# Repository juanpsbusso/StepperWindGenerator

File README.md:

# Stepper Wind Generator o Generador Eólico DIY con Motor Paso a Paso

Este proyecto detalla la construcción de un generador eólico compacto y de bajo coste, diseñado para montarse en cualquier lugar y alimentar luces LED decorativas o un circuito de carga de baterías. Utiliza un motor paso a paso trifásico como generador, aprovechando su capacidad para generar tensión a bajas RPM.

## Motivación y Contexto

Vivo en una zona con vientos constantes. La idea de este proyecto surgió al ver el viento y pensar que podría tener una aplicación práctica y visual. Este pequeño generador, montado en el auto, no solo enciende unas luces LED para darle un aspecto genial, sino que la intensidad de las luces o la cantidad de LEDs que se encienden nos permite inferir la velocidad relativa del viento, convirtiéndolo en un 'anemómetro lumínico' visual.

## ¿Cómo Funciona?

## Principio de Generación

El corazón del sistema es un motor paso a paso. Cuando el eje del motor es girado por la fuerza del viento (mediante las aspas), el motor actúa como un generador de corriente alterna (AC). Dependiendo del modelo de motor, este entregará una tensión alterna multifásica. En mi caso, el motor específico que estoy utilizando es de tres fases, por lo que genera corriente alterna trifásica.

## El Corazón Eléctrico (El Rectificador Trifásico)

Para poder alimentar dispositivos de corriente continua (DC), como luces LED o cargar una batería, necesitamos convertir la AC trifásica que entrega el motor en una tensión DC estable. Para ello, he diseñado e implementado un rectificador trifásico de onda completa.

Utilicé una simulación (ver la Figura 1) para validar el diseño antes de construirlo. El circuito incluye:

* Un puente de diodos Schottky de baja caída (D1-D6) para rectificar la señal.

* Un regulador de tensión ajustable (U1, LM317H) para controlar la tensión de salida.

* Un circuito de control de carga basado en un transistor (Q1) y resistencias ajustables, diseñado originalmente para cargar una batería de 3.7V. Este circuito se puede adaptar fácilmente para controlar la intensidad de las luces LED.

<p align="center">
  <em>Figura 1: Esquema de simulación del rectificador trifásico de onda completa.</em>
</p>

## De la Simulación a la Realidad: PCB y Perfboard

Para pasar del diseño al prototipo, realicé el diseño de una placa de circuito impreso (PCB) utilizando KiCad. El diseño de la PCB está disponible en la carpeta hw/ del repositorio para aquellos que deseen fabricarlo.

<p align="center">
  <em>Figura 2: PCB diseñado en KiCad.</em>
</p>

Sin embargo, para la construcción inicial y pruebas rápidas, decidí armar el circuito en una perfboard (ver Figura 3). Esto demuestra la viabilidad del diseño incluso sin una fabricación de PCB profesional, utilizando componentes estándar y soldadura punto a punto.

<p align="center">
  <em>Figura 3: Vista detallada del prototipo físico montado en perfboard y su conexión a los módulos LED.</em>
</p>

| Componente | Descripción | Cantidad |
| :--- | :--- | :--- |
| **D1-D6** | 1N5819G (Diodos Schottky) | 6 |
| **C1** | 10µF (Capacitor de desacoplo) | 1 |
| **-** | Placas LED (extraídas de óptica de vehículo) | 2 |
| **-** | Motor Paso a Paso (Modelo trifásico) | 1 |
| **-** | Perfboard o placa virgen para PCB | 1 |

## Futuras Mejoras

* Circuito de carga: Implementar el circuito completo de la simulación con el LM317 para poder cargar pequeñas baterías de litio.

* Integración de medición digital: Implementar un medidor de tensión digital, con un microcontrolador, para monitorear la batería o la tensión generada.

* Carcasa impermeable: Diseñar una carcasa 3D para proteger todo el sistema electrónico de las inclemencias del tiempo.

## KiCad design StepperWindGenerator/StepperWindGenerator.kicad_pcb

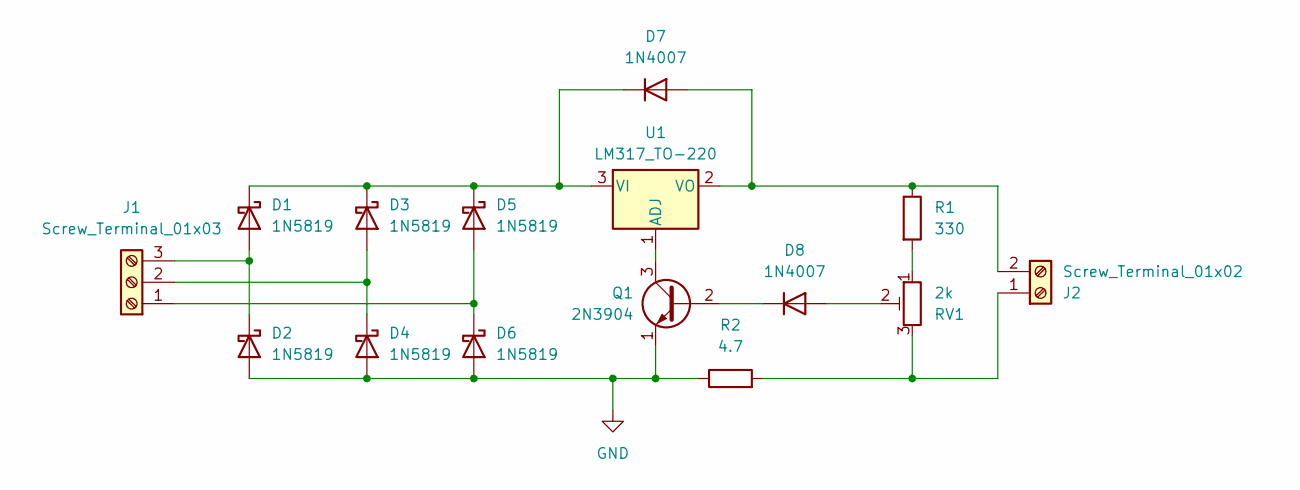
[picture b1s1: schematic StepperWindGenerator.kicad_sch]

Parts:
D1, D2, D3, D4, D5, D6: 1N5819; D_DO-41_SOD81_P10.16mm_Horizontal
D7, D8: 1N4007; D_DO-41_SOD81_P10.16mm_Horizontal
J1: Screw_Terminal_01x03; TerminalBlock_Phoenix_MKDS-1,5-3_1x03_P5.00mm_Horizontal
J2: Screw_Terminal_01x02; TerminalBlock_Phoenix_MKDS-1,5-2_1x02_P5.00mm_Horizontal
Q1: 2N3904; TO-92_Inline
R1: 330; R_Axial_DIN0204_L3.6mm_D1.6mm_P7.62mm_Horizontal
R2: 4.7; R_Axial_DIN0204_L3.6mm_D1.6mm_P7.62mm_Horizontal
RV1: 2k; Potentiometer_Piher_PT-10-V05_Vertical
U1: LM317_TO-220; TO-220-3_Vertical

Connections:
GND: D2.2 (A), D4.2 (A), D6.2 (A), Q1.1 (E), R2.1
unnamed: D1.2 (A), D2.1 (K), J1.3
unnamed: D1.1 (K), D3.1 (K), D5.1 (K), D7.1 (K), U1.3 (VI)
unnamed: D3.2 (A), D4.1 (K), J1.2
unnamed: D5.2 (A), D6.1 (K), J1.1
unnamed: D7.2 (A), J2.2, R1.1, U1.2 (VO)
unnamed: D8.2 (A), RV1.2
unnamed: D8.1 (K), Q1.2 (B)
unnamed: J2.1, R2.2, RV1.3
unnamed: Q1.3 (C), U1.1 (ADJ)
unnamed: R1.2, RV1.1

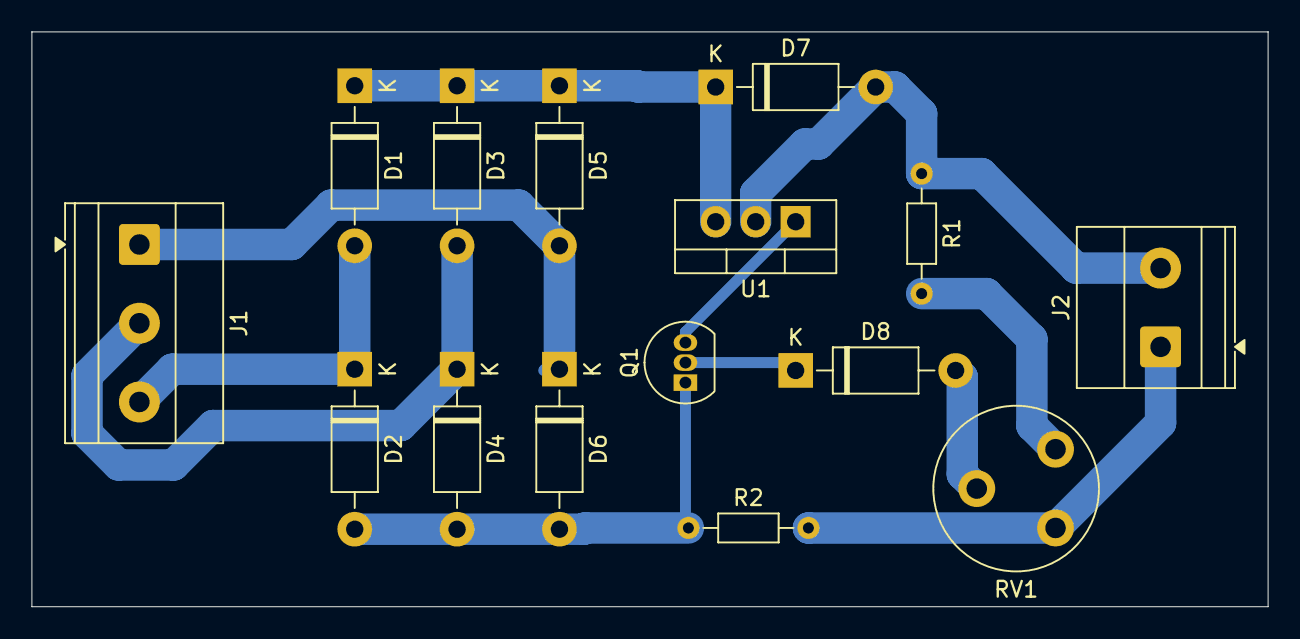
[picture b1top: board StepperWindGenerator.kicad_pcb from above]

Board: 2 copper layers, 78.5 x 36.5 mm, 15 parts (0 on the bottom side), 11 nets.

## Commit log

2026-03-20 Add KiCad files
2026-03-20 Add Multisim simulation file
